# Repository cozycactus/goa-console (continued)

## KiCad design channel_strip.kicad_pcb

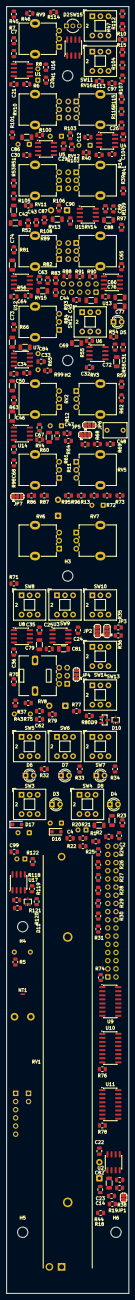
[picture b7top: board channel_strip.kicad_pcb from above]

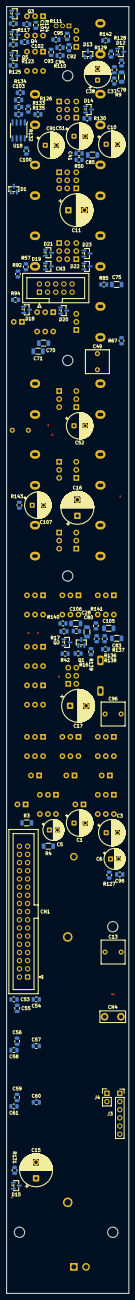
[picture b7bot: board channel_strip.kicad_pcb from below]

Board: 4 copper layers, 38.0 x 400.0 mm, 335 parts (105 on the bottom side), 195 nets, no tracks yet.

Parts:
C1, C3: 220u 25V; CP_Radial_D8.0mm_P3.50mm
C2, C4, C12, C20, C21, C22, C23, C24, C25, C26, C28, C29, C30, C31, C32, C33, C34, C35, C36, C53, C54, C55, C56, C57, C58, C59, C60, C61, C63, C64, C65, C66, C67, C68, C89, C90, C92, C93, C98, C100, C103, C104: 100n; C_0805_2012Metric
C5, C6: 47u 25V; CP_Radial_D6.3mm_P2.50mm
C7, C41: 33p C0G; C_0805_2012Metric
C10, C38, C51, C52, C91, C107: 33u NP 25V; CP_Radial_D8.0mm_P3.50mm
C11, C15, C16, C17: 100u NP 25V; CP_Radial_D10.0mm_P5.00mm
C13, C49, C96: 2.2u film; C_Rect_L7.2mm_W7.2mm_P5.00mm_FKS2_FKP2_MKS2_MKP2
C14, C94, C95: 100p C0G; C_0805_2012Metric
C37: 22p C0G; C_0805_2012Metric
C42, C43, C45: 4n7 C0G; C_1206_3216Metric
C44: 2n2 C0G; C_1206_3216Metric
C46: 10n C0G; C_1206_3216Metric
C47: 22n C0G; C_1206_3216Metric
C48: 150n film; C_Rect_L7.2mm_W4.5mm_P5.00mm_FKS2_FKP2_MKS2_MKP2
C50, C87, C88: 100n C0G; C_1206_3216Metric
C62: 1u; C_0805_2012Metric
C69, C70, C71, C72, C74, C76, C79, C80, C81, C82, C86: 10p C0G; C_1206_3216Metric
C73, C75, C77, C83, C85, C105, C106: 22p C0G; C_1206_3216Metric
C78: 33p C0G; C_1206_3216Metric
C84: 100p C0G; C_1206_3216Metric
C97, C99: 220n; C_0805_2012Metric
C101, C102: 10n; C_0805_2012Metric
CN1: Bus 2x17; IDC-Header_2x17_P2.54mm_Vertical
CN3: Jack board link 2x5; IDC-Header_2x05_P2.54mm_Vertical
CN4: Ground spade 6.3mm; Keystone_1287-ST_FastOn_Tab_6.35mm
D1, D12, D13, D14, D15: BAV99; SOT-23
D2: OL red / SIG green; LED_D3.0mm-3_P2.00mm
D3: PFL red; LED_D3.0mm
D4: ON green; LED_D3.0mm
D5: EQ green; LED_D3.0mm
D6: L-R yellow; LED_D3.0mm
D7: 1-2 yellow; LED_D3.0mm
D8: 3-4 yellow; LED_D3.0mm
D9: BZX84C5V1; SOT-23
D10, D11: BAT54W; SOT-323_SC-70
D16, D17: MBR140SFT1G; D_SOD-123F
D18, D19, D20, D21, D22, D23: BAV199; SOT-23
H1, H2, H3, H4, H5, H6: M3 standoff 11.5 mm; MountingHole_3.2mm_M3
J3: VCA module socket; PinSocket_1x06_P2.54mm_Vertical
J4: VCA control in; PinHeader_1x02_P2.54mm_Vertical
JP1: VCA bypass; SolderJumper-2_P1.3mm_Bridged_RoundedPad1.0x1.5mm
JP2: Aux1/2 pre source; SolderJumper-3_P1.3mm_Bridged12_RoundedPad1.0x1.5mm
JP3: Aux3/4 pre source; SolderJumper-3_P1.3mm_Bridged12_RoundedPad1.0x1.5mm
JP4: Aux5/6 pre source; SolderJumper-3_P1.3mm_Bridged12_RoundedPad1.0x1.5mm
JP5: Insert send source; SolderJumper-3_P1.3mm_Bridged12_RoundedPad1.0x1.5mm
JP6: EQ input; SolderJumper-3_P1.3mm_Bridged12_RoundedPad1.0x1.5mm
JP7: PRE source; SolderJumper-3_P1.3mm_Bridged12_RoundedPad1.0x1.5mm
NT1: AGND-LGND star; NetTie-2_SMD_Pad0.5mm
Q1, Q2: MMBFJ112; SOT-23
Q3, Q4, Q5: MMBT3906; SOT-23
R1, R2, R3, R4: 10R; R_1206_3216Metric
R5: 10R GND cancel; R_0805_2012Metric
R6, R7, R8, R9: 10K 0.1%; R_0805_2012Metric
R10, R112, R115, R121, R142: 1M; R_0805_2012Metric
R11, R71, R73: 75R; R_0805_2012Metric
R12, R13, R35, R36, R37, R47, R68, R72, R116, R117, R118, R122, R123, R125, R143: 47K; R_0805_2012Metric
R14, R134: 470K; R_0805_2012Metric
R15, R16, R17, R19, R34, R43, R69, R75, R77, R79, R80, R124: 4K7; R_0805_2012Metric
R18, R33, R44, R70, R74, R76, R78: 100K; R_0805_2012Metric
R20, R21, R22, R23, R24, R25, R32, R54, R55, R58, R59, R66, R67: 22K; R_0805_2012Metric
R26, R27, R28, R29, R30, R31: 4K7 1%; R_0805_2012Metric
R38, R137, R140: 2K2; R_0805_2012Metric
R39, R99, R126, R127, R128, R129, R130, R131, R135: 1K; R_0805_2012Metric
R40, R41, R120, R138, R141: 10K; R_0805_2012Metric
R42: 220K; R_0805_2012Metric
R45, R46, R84, R93: 2K2 1%; R_0805_2012Metric
R50, R51: 33K; R_0805_2012Metric
R52: 5K6; R_0805_2012Metric
R53: 6K8; R_0805_2012Metric
R56, R57, R100, R103: 4K99 1%; R_0805_2012Metric
R60, R61: 4K22 1%; R_0805_2012Metric
R62, R63, R136, R139: 3K3; R_0805_2012Metric
R64: 1K5; R_0805_2012Metric
R65: 5K1; R_0805_2012Metric
R81, R82, R83, R85, R90, R91, R92, R94: 10K 1%; R_0805_2012Metric
R86, R87: 392R 1%; R_0805_2012Metric
R88, R89, R97, R98, R105, R108: 13K 1%; R_0805_2012Metric
R95, R96: 430R 1%; R_0805_2012Metric
R101, R102: 2K49 1%; R_0805_2012Metric
R104, R107: 330R 1%; R_0805_2012Metric
R106, R109: 5K6 1%; R_0805_2012Metric
R110, R111: 220R; R_0805_2012Metric
R113, R114: 100R; R_0805_2012Metric
R119: 750K; R_0805_2012Metric
R132: 4M99 1%; R_0805_2012Metric
R133: 10M 1%; R_0805_2012Metric
RV1: Fader 10K log 100mm; Potentiometer_Bourns_PTB0143_Slide_100mm
RV2: Aux1 10K log; Potentiometer_Alpha_RD901F-40-00D_Single_Vertical
RV3: Aux2 10K log; Potentiometer_Alpha_RD901F-40-00D_Single_Vertical
RV4: Aux3 10K log; Potentiometer_Alpha_RD901F-40-00D_Single_Vertical
RV5: Aux4 10K log; Potentiometer_Alpha_RD901F-40-00D_Single_Vertical
RV6: Aux5 10K log; Potentiometer_Alpha_RD901F-40-00D_Single_Vertical
RV7: Aux6 10K log; Potentiometer_Alpha_RD901F-40-00D_Single_Vertical
RV8: Pan 10K lin dual CD; Potentiometer_Alps_RK09L_Double_Vertical
RV9: Gain 10K lin CD; Potentiometer_Alpha_RD901F-40-00D_Single_Vertical
RV10: HF 10K lin CD; Potentiometer_Alpha_RD901F-40-00D_Single_Vertical
RV11: HI-MID gain 10K lin CD; Potentiometer_Alpha_RD901F-40-00D_Single_Vertical
RV12: HI-MID freq 10K A dual; Potentiometer_Alpha_RD902F-40-00D_Dual_Vertical
RV13: LO-MID gain 10K lin CD; Potentiometer_Alpha_RD901F-40-00D_Single_Vertical
RV14: LO-MID freq 10K A dual; Potentiometer_Alpha_RD902F-40-00D_Dual_Vertical
RV15: LF 10K lin CD; Potentiometer_Alpha_RD901F-40-00D_Single_Vertical
RV16: HPF freq 10K A dual; Potentiometer_Alpha_RD902F-40-00D_Dual_Vertical
SW3: PFL; SW_Push_2P2T_Toggle_CK_PVA2xxH1xxxxxxV2
SW4: ON; SW_Push_2P2T_Toggle_CK_PVA2xxH1xxxxxxV2
SW5: Assign L-R; SW_Push_2P2T_Toggle_CK_PVA2xxH1xxxxxxV2
SW6: Assign 1-2; SW_Push_2P2T_Toggle_CK_PVA2xxH1xxxxxxV2
SW7: Assign 3-4; SW_Push_2P2T_Toggle_CK_PVA2xxH1xxxxxxV2
SW8: PRE 1-2; SW_Push_2P2T_Toggle_CK_PVA2xxH1xxxxxxV2
SW9: PRE 3-4; SW_Push_2P2T_Toggle_CK_PVA2xxH1xxxxxxV2
SW10: PRE 5-6; SW_Push_2P2T_Toggle_CK_PVA2xxH1xxxxxxV2
SW11: HPF; SW_Push_2P2T_Toggle_CK_PVA2xxH1xxxxxxV2
SW12: EQ; SW_Push_2P2T_Toggle_CK_PVA2xxH1xxxxxxV2
SW13: DIR; SW_Push_2P2T_Toggle_CK_PVA2xxH1xxxxxxV2
SW14: PAN; SW_Push_2P2T_Toggle_CK_PVA2xxH1xxxxxxV2
SW15: Phase; SW_Push_2P2T_Toggle_CK_PVA2xxH1xxxxxxV2
U1, U2, U3, U5, U6, U7, U8, U12, U13, U14, U15: OPA1612; SOIC-8_3.9x4.9mm_P1.27mm
U4, U17, U18: LM393; SOIC-8_3.9x4.9mm_P1.27mm
U9, U10, U11: DG413; SOIC-16_3.9x9.9mm_P1.27mm
U16: OPA1656; SOIC-8_3.9x4.9mm_P1.27mm

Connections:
+5VL: C55.1, C58.1, C61.1, C62.1, D9.3, D10.1, R80.2, SW5.1, SW6.1, SW7.1, U9.12, U10.12, U11.12
+VA: C1.1, C2.1, C20.1, C22.1, C24.1, C29.1, C31.1, C33.1, C35.1, C53.1, C56.1, C59.1, C63.1, C65.1, C67.1, C89.1, C92.1, D10.3, D16.1, D18.2, D19.2, D20.2, D21.2, D22.2, D23.2, J3.4, R1.2, R80.1, U1.8, U2.8, U3.8, U5.8, U6.8, U7.8, U8.8, U9.13, U10.13, U11.13, U12.8, U13.8, U14.8, U15.8, U16.8
+VBUS: CN1.32, CN1.33, CN1.34, R1.1, R3.1
+VL: C5.1, C26.1, C98.1, C101.2, C102.2, C104.1, Q3.2, Q4.2, Q5.2, R3.2, R40.1, R115.1, R117.1, R121.1, R123.1, R132.1, SW3.5, SW4.5, SW5.5, SW6.5, SW7.5, SW12.5, U4.8, U17.8, U18.8
-VA: C3.2, C4.2, C21.2, C23.2, C25.2, C30.2, C32.2, C34.2, C36.2, C54.2, C57.2, C60.2, C64.2, C66.2, C68.2, C90.2, C93.2, D17.2, D18.1, D19.1, D20.1, D21.1, D22.1, D23.1, J3.6, R2.2, U1.4, U2.4, U3.4, U5.4, U6.4, U7.4, U8.4, U9.4, U10.4, U11.4, U12.4, U13.4, U14.4, U15.4, U16.4
-VBUS: CN1.30, CN1.31, R2.1, R4.1
-VL: C6.2, R4.2, SW4.1
A6R: R25.1, SW13.3, SW13.5
AUX1: CN1.24, R20.2
AUX2: CN1.25, R21.2
AUX3: CN1.23, R22.2
AUX4: CN1.22, R23.2
AUX5: CN1.21, R24.2
AUX6: CN1.20, R25.2
BUF1: JP6.3, JP7.1, U7.6, U7.7
DIRSRC: C83.1, R70.1, SW13.1, U8.3
DO_R: CN3.9, D23.3, R73.1, R143.1
DO_T: C52.2, CN3.8, D22.3, R72.1
EQIN: JP6.2, R50.1, RV10.3, SW12.3
EQOUT: C51.2, JP5.1, JP7.3, R68.1, R130.1
EQ_FP: C49.2, C50.1, R65.1, U7.3
EQ_LP: C46.1, R93.1, R98.1, RV14.6, U6.5, U14.1
EQ_MP: C44.1, R84.1, R89.1, RV12.6, U6.3, U12.7
EQ_O6: C73.1, R63.2, R67.1, SW12.1, U7.1
EQ_WHM: R81.1, RV11.2
EQ_WLM: R90.1, RV13.2
FPIN: C82.1, J3.2, JP1.2, R18.1, U2.3
FPOST: C14.1, C15.1, R19.1, R131.1, U2.1
GCANCEL: CN1.26, R5.2
GNDA: C1.2, C2.2, C3.1, C4.1, C12.2, C20.2, C21.1, C22.2, C23.1, C24.2, C25.1, C28.2, C29.2, C30.1, C31.2, C32.1, C33.2, C34.1, C35.2, C36.1, C50.2, C53.2, C54.1, C56.2, C57.1, C59.2, C60.1, C63.2, C64.1, C65.2, C66.1, C67.2, C68.1, C75.2, C77.2, C78.2, C79.2, C80.2, C81.2, C82.2, C83.2, C84.2, C85.2, C89.2, C90.1, C92.2, C93.1, C94.2, C95.2, C100.2, C103.2, C107.2, CN1.2, CN1.4, CN1.6, CN1.8, CN1.10, CN1.12, CN1.14, CN1.16, CN3.3, CN3.5, CN3.7, CN3.10, CN4.1, D16.2, D17.1, J3.5, J4.2, NT1.1, Q1.2, Q2.2, R5.1, R9.2, R10.2, R12.2, R13.2, R14.2, R18.2, R35.2, R36.2, R37.2, R38.2, R41.2, R44.2, R47.2, R52.2, R65.2, R68.2, R70.2, R72.2, R85.2, R86.2, R87.2, R94.2, R95.2, R96.2, R104.2, R107.2, R112.2, R120.2, R134.2, R138.1, R141.1, R143.2, RV1.1, RV2.1, RV3.1, RV4.1, RV5.1, RV6.1, RV7.1, RV8.3, RV8.4, SW3.3, SW13.4, U1.5, U2.5, U5.5, U9.10, U9.15, U10.10, U10.15, U11.10, U11.15, U12.5, U13.3, U14.3, U14.5, U15.3, U15.5
GNDD: C5.2, C6.1, C26.2, C55.2, C58.2, C61.2, C62.2, C97.2, C98.2, C99.2, C104.2, D2.2, D3.1, D4.1, D5.1, D6.1, D7.1, D8.1, D9.1, D11.1, NT1.2, R74.2, R76.2, R78.2, SW4.3, SW5.3, SW6.3, SW7.3, U4.4, U9.5, U10.5, U11.5, U17.4, U18.4, U18.6
GOUT: C37.1, C38.1, C91.1, R46.2, R129.1, R142.2, U1.7
HIN: C38.2, C91.2, R47.1, R100.1, SW11.3
HOUT: JP2.3, JP3.3, JP4.3, JP5.3, JP6.1, SW11.2
INS_SRC: JP5.2, R11.1
IN_R: CN3.2, D19.3, R111.1, R112.1
IN_T: CN3.1, D18.3, R10.1, R110.1
MIXL: CN1.18, U9.2
MIXR: CN1.17, U9.7
MUTEOUT: JP2.1, JP3.1, JP4.1, RV1.3, U3.6, U3.7
unnamed: C10.2, R12.1, R99.1
unnamed: C13.1, RV1.2
unnamed: C41.1, C69.1, R51.1, R54.1, RV10.1, RV11.1, U5.7
unnamed: C42.1, RV10.2
unnamed: C42.2, C43.1, R52.1
unnamed: C43.2, R53.1
unnamed: C45.1, R82.1, U13.1
unnamed: C47.1, R91.1, U14.7
unnamed: C48.1, R62.2, RV15.1
unnamed: C48.2, R63.1, RV15.3
unnamed: C49.1, R64.2
unnamed: C52.1, R71.2
unnamed: C70.1, C71.1, R55.1, R58.1, RV11.3, RV13.1, U6.1
unnamed: C72.1, R59.1, R62.1, R66.1, RV13.3, U6.7
unnamed: C74.1, R83.1, R88.1, RV12.3, U12.1
unnamed: C76.1, R92.1, R97.1, RV14.3, U13.7
unnamed: C87.1, R101.1, R108.1, RV16.6, U15.1
unnamed: C88.1, R102.1, U15.7
unnamed: C96.2, R32.1
unnamed: C16.1, C105.2, R136.1, R137.2, U8.7
unnamed: C17.1, C106.2, R139.1, R140.2, U3.1
unnamed: C107.1, R73.2
unnamed: D1.3, R39.2
unnamed: D3.2, R34.2
unnamed: D4.2, R43.2
unnamed: D5.2, R69.2
unnamed: D6.2, R75.2
unnamed: D7.2, R77.2
unnamed: D8.2, R79.2
unnamed: D12.3, R128.2
unnamed: D13.3, R129.2
unnamed: D14.3, R130.2
unnamed: D15.3, R131.2
unnamed: JP2.2, SW8.1
unnamed: JP3.2, SW9.1
unnamed: JP4.2, SW10.1
unnamed: Q1.1, R16.2, R17.1
unnamed: C28.1, Q1.3, Q2.3, R42.2
unnamed: C81.1, Q2.1, R17.2, U3.5
unnamed: C101.1, Q3.1, R116.2, R117.2
unnamed: Q3.3, R15.1
unnamed: Q4.3, R124.1
unnamed: Q5.1, R125.2
unnamed: R20.1, RV2.2
unnamed: R21.1, RV3.2
unnamed: R22.1, RV4.2
unnamed: R23.1, RV5.2
unnamed: R24.1, RV6.2
unnamed: R26.2, U9.3, U9.14
unnamed: R27.2, U9.6, U9.11
unnamed: R28.2, U10.3, U10.14
unnamed: R29.2, U10.6, U10.11
unnamed: R30.2, U11.3, U11.14
unnamed: R31.2, U11.6, U11.11
unnamed: R45.2, RV9.3
unnamed: R46.1, RV9.1
unnamed: R56.1, R88.2, RV12.2
unnamed: R57.1, R89.2, RV12.5
unnamed: R60.1, R97.2, RV14.2
unnamed: R61.1, R98.2, RV14.5
unnamed: R64.1, RV15.2
unnamed: R86.1, RV12.1
unnamed: R87.1, RV12.4
unnamed: R95.1, RV14.1
unnamed: R96.1, RV14.4
unnamed: R104.1, RV16.1
unnamed: R105.2, R106.1, RV16.2
unnamed: R107.1, RV16.4
unnamed: R108.2, R109.1, RV16.5
unnamed: R122.1, U17.7
unnamed: R126.1, U4.1
unnamed: R127.1, U17.1
unnamed: R135.1, U18.1
unnamed: R32.2, SW3.2
unnamed: R33.1, R34.1, SW3.4
unnamed: R42.1, SW4.2
unnamed: R43.1, SW4.4
unnamed: R75.1, SW5.4
unnamed: R77.1, SW6.4
unnamed: R79.1, SW7.4
unnamed: RV2.3, RV3.3, SW8.2
unnamed: RV4.3, RV5.3, SW9.2
unnamed: RV6.3, RV7.3, SW10.2
unnamed: C86.1, R103.1, R105.1, RV16.3, SW11.1, U5.1
unnamed: C51.1, SW12.2
unnamed: R69.1, SW12.4
unnamed: RV7.2, SW13.2
unnamed: R114.2, SW15.1, SW15.6
unnamed: R6.1, SW15.2
unnamed: R113.2, SW15.3, SW15.4
unnamed: R8.1, SW15.5
unnamed: C78.1, R8.2, R9.1, U1.3
unnamed: C7.1, R6.2, R7.1, U1.2
unnamed: C37.2, R142.1, RV9.2, U1.6
unnamed: C14.2, R19.2, R38.1, U2.2
unnamed: U2.6, U2.7
unnamed: C80.1, R139.2, RV8.5, U3.3
unnamed: C106.1, R140.1, R141.2, U3.2
unnamed: C85.1, R100.2, R101.2, U5.3
unnamed: C86.2, R102.2, R103.2, U5.2
unnamed: C41.2, R50.2, R51.2, R53.2, U5.6
unnamed: C69.2, C70.2, R54.2, R55.2, U6.2
unnamed: C71.2, C72.2, R58.2, R59.2, U6.6
unnamed: C73.2, R66.2, R67.2, U7.2
unnamed: C84.1, R99.2, U7.5
unnamed: R71.1, U8.1, U8.2
unnamed: C79.1, R136.2, RV8.2, U8.5
unnamed: C105.1, R137.1, R138.2, U8.6
unnamed: C75.1, R84.2, R85.1, U12.3
unnamed: C74.2, R81.2, R82.2, R83.2, U12.2
unnamed: C44.2, R56.2, U12.6
unnamed: C45.2, R57.2, U13.2
unnamed: C77.1, R93.2, R94.1, U13.5
unnamed: C76.2, R90.2, R91.2, R92.2, U13.6
unnamed: C46.2, R60.2, U14.2
unnamed: C47.2, R61.2, U14.6
unnamed: C87.2, R106.2, U15.2
unnamed: C88.2, R109.2, U15.6
unnamed: C94.1, R110.2, U16.3
unnamed: R113.1, U16.1, U16.2
unnamed: C95.1, R111.2, U16.5
unnamed: R114.1, U16.6, U16.7
unnamed: R119.2, R120.1, U17.3
unnamed: C99.1, R121.2, R127.2, U17.5
unnamed: R132.2, R133.1, U18.3
OL_A: D2.1, R15.2
OL_HOLD: C97.1, R115.2, R126.2, R135.2, U4.5
OL_K: R116.1, R125.1, U4.7
OL_NN: C103.1, D1.1, D12.1, D13.1, D14.1, D15.1, R133.2, R134.1
PANL: C16.2, R26.1, R36.1, SW14.1
PANR: C17.2, R27.1, R37.1, SW14.4
PFL: CN1.27, SW3.1
PFLDET: CN1.29, R33.2
PK: C12.1, D1.2, D12.2, D13.2, D14.2, D15.2, R14.1, U4.2
POST: C15.2, R35.1, RV8.1, RV8.6, SW8.3, SW9.3, SW10.3, SW14.3, SW14.6
PRE: C11.2, C96.1, R13.1, R16.1
PRESRC: C11.1, JP7.2, R39.1, R118.1
RECV: C7.2, R7.2, R45.1, R128.1, U1.1
RET_RAW: C10.1, CN3.6, D20.3
RTE_12: R76.1, SW6.2, U10.1, U10.8, U10.9, U10.16
RTE_34: R78.1, SW7.2, U11.1, U11.8, U11.9, U11.16
RTE_LR: R74.1, SW5.2, U9.1, U9.8, U9.9, U9.16
SEND: CN3.4, D21.3, R11.2
SIG_A: D2.3, R124.2
SIG_B: C102.1, Q4.1, Q5.3, R122.2, R123.2
SIG_IN: D11.3, R118.2, U17.2
SUB1: CN1.15, U10.2
SUB2: CN1.13, U10.7
SUB3: CN1.11, U11.2
SUB4: CN1.9, U11.7
SUBSRC_L: R28.1, R30.1, SW14.2
SUBSRC_R: R29.1, R31.1, SW14.5
VCAIN: C13.2, J3.1, JP1.1
VCA_CTRL: J3.3, J4.1, R44.1
VREF: C100.1, R40.2, R41.1, R119.1, U4.3, U4.6, U17.6, U18.2, U18.5

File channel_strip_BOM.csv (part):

"Qty","Value","Footprint","MPN","DNP","References"
"2","220u 25V","Capacitor_THT:CP_Radial_D8.0mm_P3.50mm","Rubycon 35ZLH220MEFC8X11.5 (35V)","","C1 C3"
"42","100n","Capacitor_SMD:C_0805_2012Metric","Samsung CL21B104KBCNNNC (X7R 50V)","","C2 C4 C12 C20 C21 C22 C23 C24 C25 C26 C28 C29 C30 C31 C32 C33 C34 C35 C36 C53 C54 C55 C56 C57 C58 C59 C60 C61 C63 C64 C65 C66 C67 C68 C89 C90 C92 C93 C98 C100 C103 C104"
"2","47u 25V","Capacitor_THT:CP_Radial_D6.3mm_P2.50mm","Panasonic EEU-FR1H470 (50V)","","C5 C6"
"2","33p C0G","Capacitor_SMD:C_0805_2012Metric","KEMET C0805C330J5GACTU","","C7 C41"
"6","33u NP 25V","Capacitor_THT:CP_Radial_D8.0mm_P3.50mm","Nichicon UES1E330MPM (MUSE ES)","","C10 C38 C51 C52 C91 C107"
"4","100u NP 25V","Capacitor_THT:CP_Radial_D10.0mm_P5.00mm","Nichicon UES1E101MPM (MUSE ES)","","C11 C15 C16 C17"
"3","2.2u film","Capacitor_THT:C_Rect_L7.2mm_W7.2mm_P5.00mm_FKS2_FKP2_MKS2_MKP2","KEMET MMK5225K63J06L4BULK (PET 63V; replaces the obsolete WIMA MKS2C042201K00KSSD)","","C13 C49 C96"
"3","100p C0G","Capacitor_SMD:C_0805_2012Metric","KEMET C0805C101J5GACTU","","C14 C94 C95"
"1","22p C0G","Capacitor_SMD:C_0805_2012Metric","KEMET C0805C220J5GACTU","","C37"
"3","4n7 C0G","Capacitor_SMD:C_1206_3216Metric","KEMET C1206C472J5GACTU","","C42 C43 C45"
"1","2n2 C0G","Capacitor_SMD:C_1206_3216Metric","KEMET C1206C222J5GACTU","","C44"
"1","10n C0G","Capacitor_SMD:C_1206_3216Metric","KEMET C1206C103J5GACTU","","C46"
"1","22n C0G","Capacitor_SMD:C_1206_3216Metric","KEMET C1206C223J5GACTU","","C47"
"1","150n film","Capacitor_THT:C_Rect_L7.2mm_W4.5mm_P5.00mm_FKS2_FKP2_MKS2_MKP2","WIMA MKS2D031501C00KSSD (PET 100V; 3.5 x 8.5 x 7.2, the 63 V KSSD code has no stock)","","C48"
"3","100n C0G","Capacitor_SMD:C_1206_3216Metric","Murata GRM31C5C1H104JA01L","","C50 C87 C88"
"1","1u","Capacitor_SMD:C_0805_2012Metric","Murata GRM21BR71H105KA12L (X7R 50V)","","C62"
"11","10p C0G","Capacitor_SMD:C_1206_3216Metric","KEMET C1206C100J5GACTU","","C69 C70 C71 C72 C74 C76 C79 C80 C81 C82 C86"
"7","22p C0G","Capacitor_SMD:C_1206_3216Metric","KEMET C1206C220J5GACTU","","C73 C75 C77 C83 C85 C105 C106"
"1","33p C0G","Capacitor_SMD:C_1206_3216Metric","KEMET C1206C330J5GACTU","","C78"
"1","100p C0G","Capacitor_SMD:C_1206_3216Metric","KEMET C1206C101J5GACTU","","C84"
"2","220n","Capacitor_SMD:C_0805_2012Metric","Samsung CL21B224KBFNNNE (X7R 50V)","","C97 C99"
"2","10n","Capacitor_SMD:C_0805_2012Metric","Samsung CL21B103KBANNNC (X7R 50V)","","C101 C102"
"1","Bus 2x17","Connector_IDC:IDC-Header_2x17_P2.54mm_Vertical","Wurth 61203421621 (2x17 box header)","","CN1"
"1","Jack board link 2x5","Connector_IDC:IDC-Header_2x05_P2.54mm_Vertical","Wurth 61201021621 (2x5 box header)","","CN3"
"1","Ground spade 6.3mm","goa-console:Keystone_1287-ST_FastOn_Tab_6.35mm","Keystone 1287-ST","","CN4"
"5","BAV99","Package_TO_SOT_SMD:SOT-23","Nexperia BAV99,215","","D1 D12 D13 D14 D15"
"1","OL red / SIG green","goa-console:LED_D3.0mm-3_P2.00mm","Kingbright WP3VEGW","","D2"
"1","PFL red","LED_THT:LED_D3.0mm","Kingbright WP710A10ID","","D3"
"1","ON green","LED_THT:LED_D3.0mm","Kingbright WP710A10GD","","D4"
"1","EQ green","LED_THT:LED_D3.0mm","Kingbright WP710A10GD","","D5"
"1","L-R yellow","LED_THT:LED_D3.0mm","Kingbright WP710A10YD","","D6"
"1","1-2 yellow","LED_THT:LED_D3.0mm","Kingbright WP710A10YD","","D7"
"1","3-4 yellow","LED_THT:LED_D3.0mm","Kingbright WP710A10YD","","D8"
"1","BZX84C5V1","Package_TO_SOT_SMD:SOT-23","Nexperia BZX84-C5V1,215","","D9"
"2","BAT54W","Package_TO_SOT_SMD:SOT-323_SC-70","Nexperia BAT54W,115","","D10 D11"
"2","PMEG4010CEH","Diode_SMD:D_SOD-123F","Nexperia PMEG4010CEH,115","","D16 D17"
"6","BAV199","Package_TO_SOT_SMD:SOT-23","Nexperia BAV199,215","","D18 D19 D20 D21 D22 D23"
"1","VCA module socket","Connector_PinSocket_2.54mm:PinSocket_1x06_P2.54mm_Vertical","","DNP","J3"
"1","VCA control in","Connector_PinHeader_2.54mm:PinHeader_1x02_P2.54mm_Vertical","","DNP","J4"
"2","MMBFJ112","Package_TO_SOT_SMD:SOT-23","onsemi MMBFJ112","","Q1 Q2"
"3","MMBT3906","Package_TO_SOT_SMD:SOT-23","onsemi MMBT3906LT1G","","Q3 Q4 Q5"
"4","10R","Resistor_SMD:R_1206_3216Metric","Vishay M251206BB1009JP500","","R1 R2 R3 R4"
"1","10R GND cancel","Resistor_SMD:R_0805_2012Metric","","","R5"
"4","10K 0.1%","Resistor_SMD:R_0805_2012Metric","Panasonic ERA-6AEB103V","","R6 R7 R8 R9"
"5","1M","Resistor_SMD:R_0805_2012Metric","","","R10 R112 R115 R121 R142"
"3","75R","Resistor_SMD:R_0805_2012Metric","Panasonic ERJ-P06J750V","","R11 R71 R73"
"15","47K","Resistor_SMD:R_0805_2012Metric","","","R12 R13 R35 R36 R37 R47 R68 R72 R116 R117 R118 R122 R123 R125 R143"
"2","470K","Resistor_SMD:R_0805_2012Metric","","","R14 R134"
"12","4K7","Resistor_SMD:R_0805_2012Metric","","","R15 R16 R17 R19 R34 R43 R69 R75 R77 R79 R80 R124"
"6","100K","Resistor_SMD:R_0805_2012Metric","","","R18 R33 R70 R74 R76 R78"
"13","22K","Resistor_SMD:R_0805_2012Metric","","","R20 R21 R22 R23 R24 R25 R32 R54 R55 R58 R59 R66 R67"
"6","4K7 1%","Resistor_SMD:R_0805_2012Metric","","","R26 R27 R28 R29 R30 R31"
"3","2K2","Resistor_SMD:R_0805_2012Metric","","","R38 R137 R140"
"9","1K","Resistor_SMD:R_0805_2012Metric","","","R39 R99 R126 R127 R128 R129 R130 R131 R135"
"5","10K","Resistor_SMD:R_0805_2012Metric","","","R40 R41 R120 R138 R141"
"1","220K","Resistor_SMD:R_0805_2012Metric","","","R42"
"1","100K","Resistor_SMD:R_0805_2012Metric","","DNP","R44"
"4","2K2 1%","Resistor_SMD:R_0805_2012Metric","","","R45 R46 R84 R93"
"2","33K","Resistor_SMD:R_0805_2012Metric","","","R50 R51"
"1","5K6","Resistor_SMD:R_0805_2012Metric","","","R52"
"1","6K8","Resistor_SMD:R_0805_2012Metric","","","R53"
"4","4K99 1%","Resistor_SMD:R_0805_2012Metric","","","R56 R57 R100 R103"
"2","4K22 1%","Resistor_SMD:R_0805_2012Metric","","","R60 R61"
"4","3K3","Resistor_SMD:R_0805_2012Metric","","","R62 R63 R136 R139"
"1","1K5","Resistor_SMD:R_0805_2012Metric","","","R64"
"1","5K1","Resistor_SMD:R_0805_2012Metric","","","R65"
"8","10K 1%","Resistor_SMD:R_0805_2012Metric","","","R81 R82 R83 R85 R90 R91 R92 R94"
"2","392R 1%","Resistor_SMD:R_0805_2012Metric","","","R86 R87"
"6","13K 1%","Resistor_SMD:R_0805_2012Metric","","","R88 R89 R97 R98 R105 R108"
"2","430R 1%","Resistor_SMD:R_0805_2012Metric","","","R95 R96"
"2","2K49 1%","Resistor_SMD:R_0805_2012Metric","","","R101 R102"
"2","330R 1%","Resistor_SMD:R_0805_2012Metric","","","R104 R107"
"2","5K6 1%","Resistor_SMD:R_0805_2012Metric","","","R106 R109"
"2","220R","Resistor_SMD:R_0805_2012Metric","","","R110 R111"
"2","100R","Resistor_SMD:R_0805_2012Metric","","","R113 R114"
"1","750K","Resistor_SMD:R_0805_2012Metric","","","R119"
"1","4M99 1%","Resistor_SMD:R_0805_2012Metric","","","R132"
"1","10M 1%","Resistor_SMD:R_0805_2012Metric","","","R133"
"1","Fader 10K log 100mm","goa-console:Potentiometer_Bourns_PTB0143_Slide_100mm","Bourns PTB0143-2010BPA103","","RV1"
"1","Aux1 10K log","Potentiometer_THT:Potentiometer_Alpha_RD901F-40-00D_Single_Vertical","Alpha RD901F-40-15R1-A10K","","RV2"
"1","Aux2 10K log","Potentiometer_THT:Potentiometer_Alpha_RD901F-40-00D_Single_Vertical","Alpha RD901F-40-15R1-A10K","","RV3"
"1","Aux3 10K log","Potentiometer_THT:Potentiometer_Alpha_RD901F-40-00D_Single_Vertical","Alpha RD901F-40-15R1-A10K","","RV4"
"1","Aux4 10K log","Potentiometer_THT:Potentiometer_Alpha_RD901F-40-00D_Single_Vertical","Alpha RD901F-40-15R1-A10K","","RV5"
"1","Aux5 10K log","Potentiometer_THT:Potentiometer_Alpha_RD901F-40-00D_Single_Vertical","Alpha RD901F-40-15R1-A10K","","RV6"
"1","Aux6 10K log","Potentiometer_THT:Potentiometer_Alpha_RD901F-40-00D_Single_Vertical","Alpha RD901F-40-15R1-A10K","","RV7"
"1","Pan 10K lin dual CD","Potentiometer_THT:Potentiometer_Alps_RK09L_Double_Vertical","ALPS RK09L1240015","","RV8"
"1","Gain 10K lin CD","Potentiometer_THT:Potentiometer_Alpha_RD901F-40-00D_Single_Vertical","Alpha RD901F-40-15R1-B10K-0CD (centre detent)","","RV9"
"1","HF 10K lin CD","Potentiometer_THT:Potentiometer_Alpha_RD901F-40-00D_Single_Vertical","Alpha RD901F-40-15R1-B10K-0CD (centre detent)","","RV10"
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
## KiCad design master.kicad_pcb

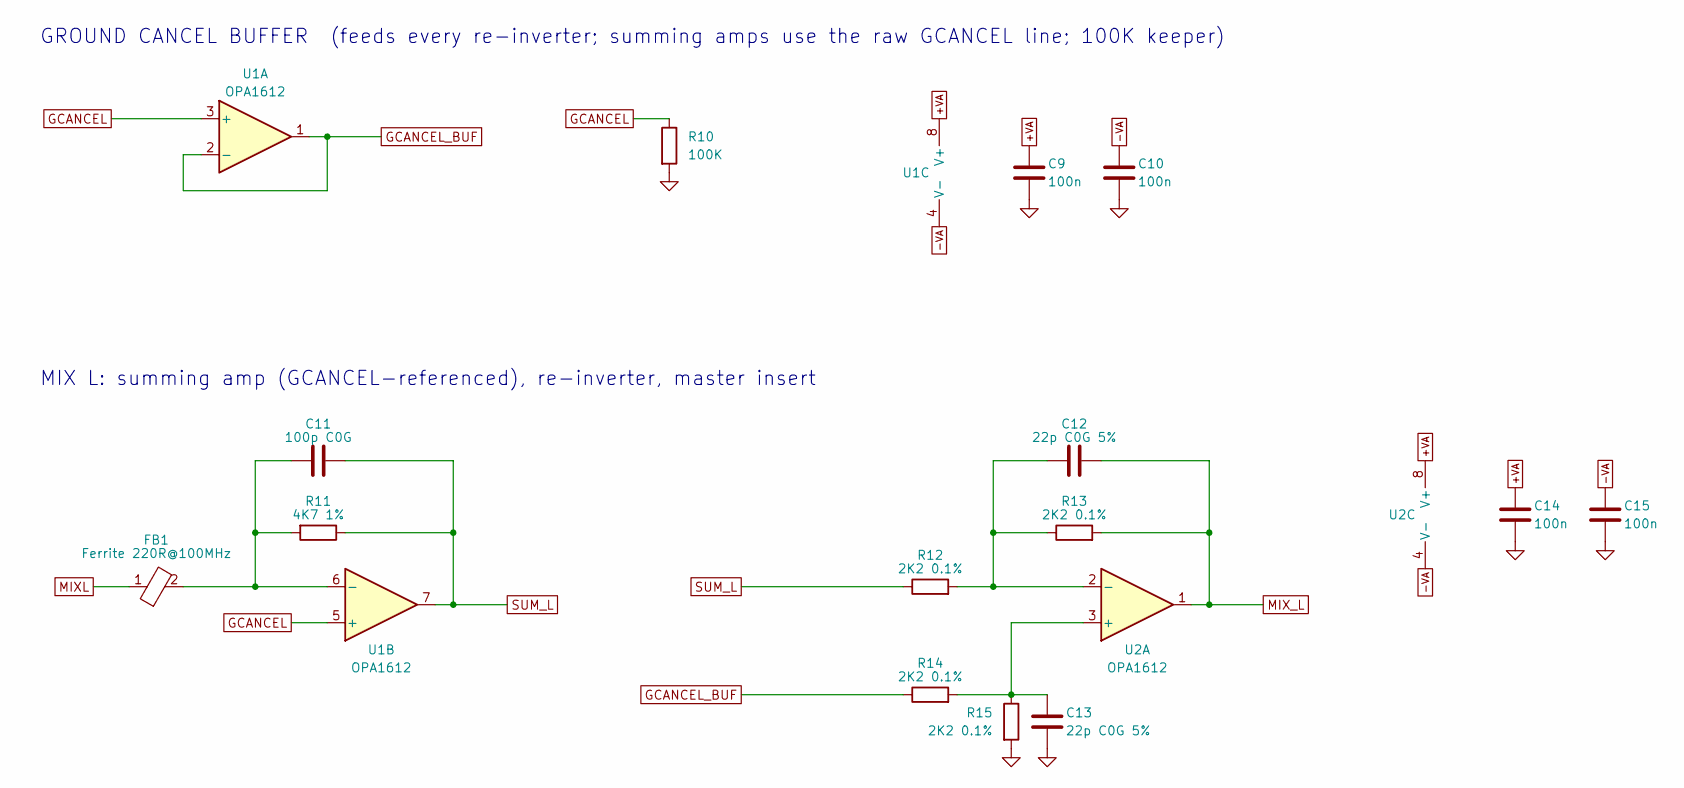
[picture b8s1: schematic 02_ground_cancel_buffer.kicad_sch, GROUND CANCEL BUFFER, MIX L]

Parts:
C9, C10, C14, C15: 100n; C_0805_2012Metric; MPN Samsung CL21B104KBCNNNC (X7R 50V)
C11: 100p C0G; C_0805_2012Metric; MPN KEMET C0805C101J5GACTU
C12, C13: 22p C0G 5%; C_0805_2012Metric; MPN KEMET C0805C220J5GACTU
FB1: Ferrite 220R@100MHz; L_0805_2012Metric; MPN Murata BLM21PG221SN1D
R10: 100K; R_0805_2012Metric
R11: 4K7 1%; R_0805_2012Metric
R12, R13, R14, R15: 2K2 0.1%; R_0805_2012Metric; MPN Panasonic ERA-6AEB222V
U1, U2: OPA1612; SOIC-8_3.9x4.9mm_P1.27mm; MPN TI OPA1612AIDR

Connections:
+VA: C9.1, C14.1, U1.8 (V+), U2.8 (V+); also elsewhere on the board
-VA: C10.2, C15.2, U1.4 (V-), U2.4 (V-); also elsewhere on the board
GCANCEL: R10.1, U1.3 (+), U1.5 (+); also elsewhere on the board
GCANCEL_BUF: R14.1, U1.1, U1.2 (-); also elsewhere on the board
MIXL: FB1.1; also elsewhere on the board
MIX_L: C12.1, R13.2, U2.1; also elsewhere on the board
unnamed: C11.2, FB1.2, R11.2, U1.6 (-)
unnamed: C13.1, R14.2, R15.1, U2.3 (+)
unnamed: C12.2, R12.2, R13.1, U2.2 (-)
SUM_L: C11.1, R11.1, R12.1, U1.7

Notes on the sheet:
GROUND CANCEL BUFFER (feeds every re-inverter; summing amps use the raw GCANCEL line; 100K keeper)
MIX L: summing amp (GCANCEL-referenced), re-inverter, master insert

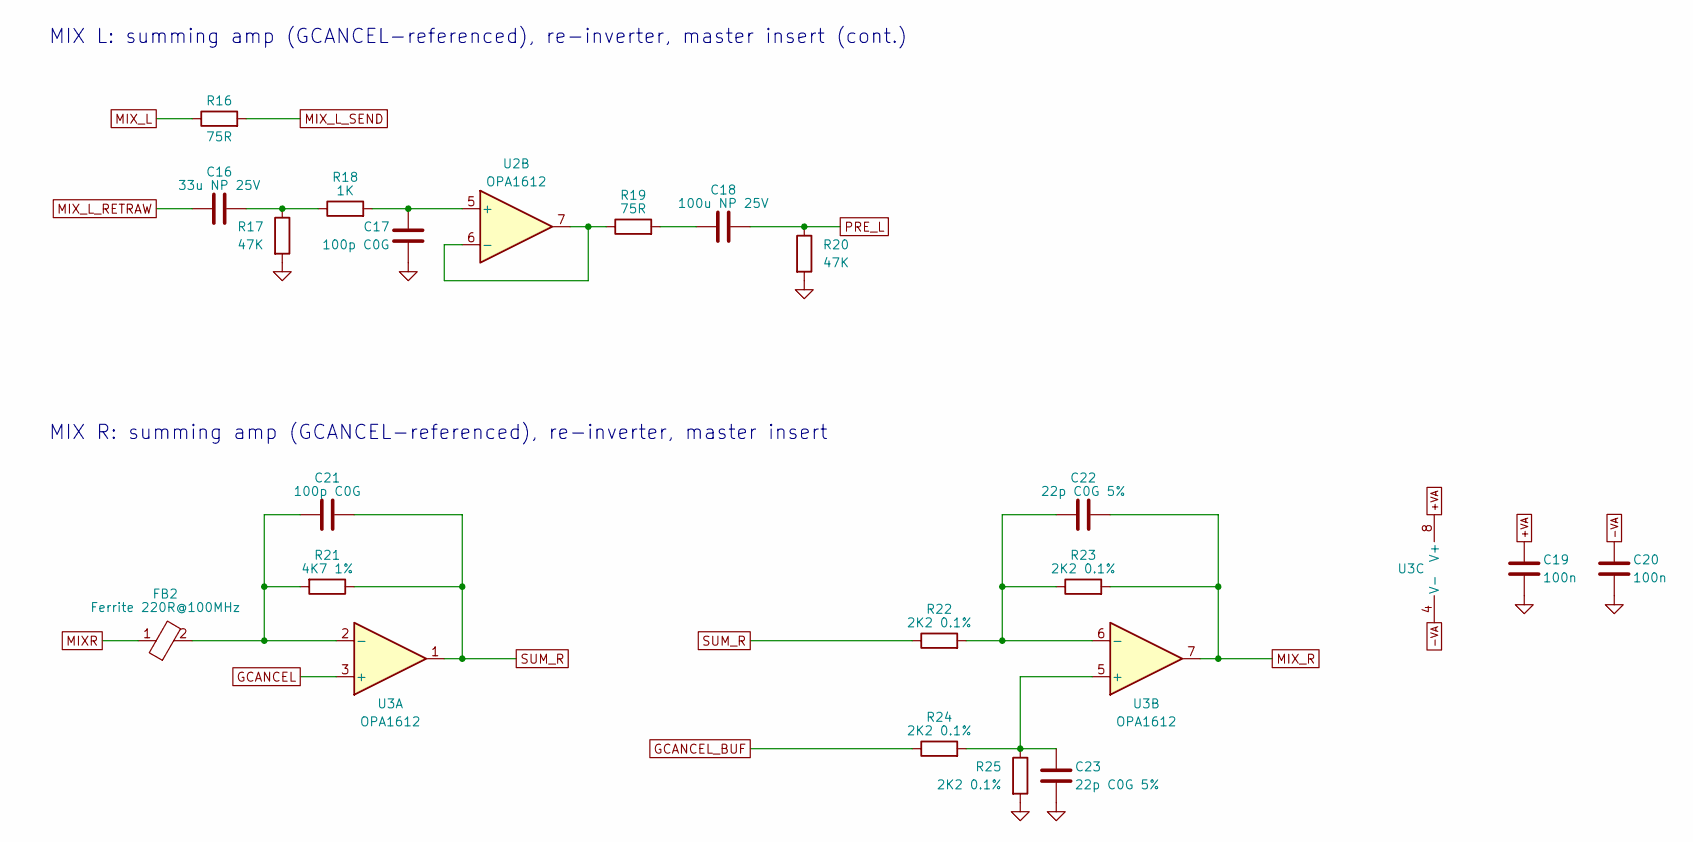
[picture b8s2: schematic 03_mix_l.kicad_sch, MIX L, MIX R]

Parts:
C16: 33u NP 25V; CP_Radial_D8.0mm_P3.50mm; MPN Nichicon UES1E330MPM (MUSE ES)
C17, C21: 100p C0G; C_0805_2012Metric; MPN KEMET C0805C101J5GACTU
C18: 100u NP 25V; CP_Radial_D10.0mm_P5.00mm; MPN Nichicon UES1E101MPM (MUSE ES)
C19, C20: 100n; C_0805_2012Metric; MPN Samsung CL21B104KBCNNNC (X7R 50V)
C22, C23: 22p C0G 5%; C_0805_2012Metric; MPN KEMET C0805C220J5GACTU
FB2: Ferrite 220R@100MHz; L_0805_2012Metric; MPN Murata BLM21PG221SN1D
R16: 75R; R_0805_2012Metric; MPN Panasonic ERJ-P06J750V
R17, R20: 47K; R_0805_2012Metric
R18: 1K; R_0805_2012Metric
R19: 75R; R_0805_2012Metric
R21: 4K7 1%; R_0805_2012Metric
R22, R23, R24, R25: 2K2 0.1%; R_0805_2012Metric; MPN Panasonic ERA-6AEB222V
U2, U3: OPA1612; SOIC-8_3.9x4.9mm_P1.27mm; MPN TI OPA1612AIDR

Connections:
+VA: C19.1, U3.8 (V+); also elsewhere on the board
-VA: C20.2, U3.4 (V-); also elsewhere on the board
GCANCEL: U3.3 (+); also elsewhere on the board
GCANCEL_BUF: R24.1; also elsewhere on the board
MIXR: FB2.1; also elsewhere on the board
MIX_L: R16.1; also elsewhere on the board
MIX_L_RETRAW: C16.1; also elsewhere on the board
MIX_L_SEND: R16.2; also elsewhere on the board
MIX_R: C22.1, R23.2, U3.7; also elsewhere on the board
unnamed: C16.2, R17.1, R18.1
unnamed: C18.1, R19.2
unnamed: C17.1, R18.2, U2.5 (+)
unnamed: R19.1, U2.6 (-), U2.7
unnamed: C21.2, FB2.2, R21.2, U3.2 (-)
unnamed: C23.1, R24.2, R25.1, U3.5 (+)
unnamed: C22.2, R22.2, R23.1, U3.6 (-)
PRE_L: C18.2, R20.1; also elsewhere on the board
SUM_R: C21.1, R21.1, R22.1, U3.1

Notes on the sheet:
MIX L: summing amp (GCANCEL-referenced), re-inverter, master insert (cont.)
MIX R: summing amp (GCANCEL-referenced), re-inverter, master insert

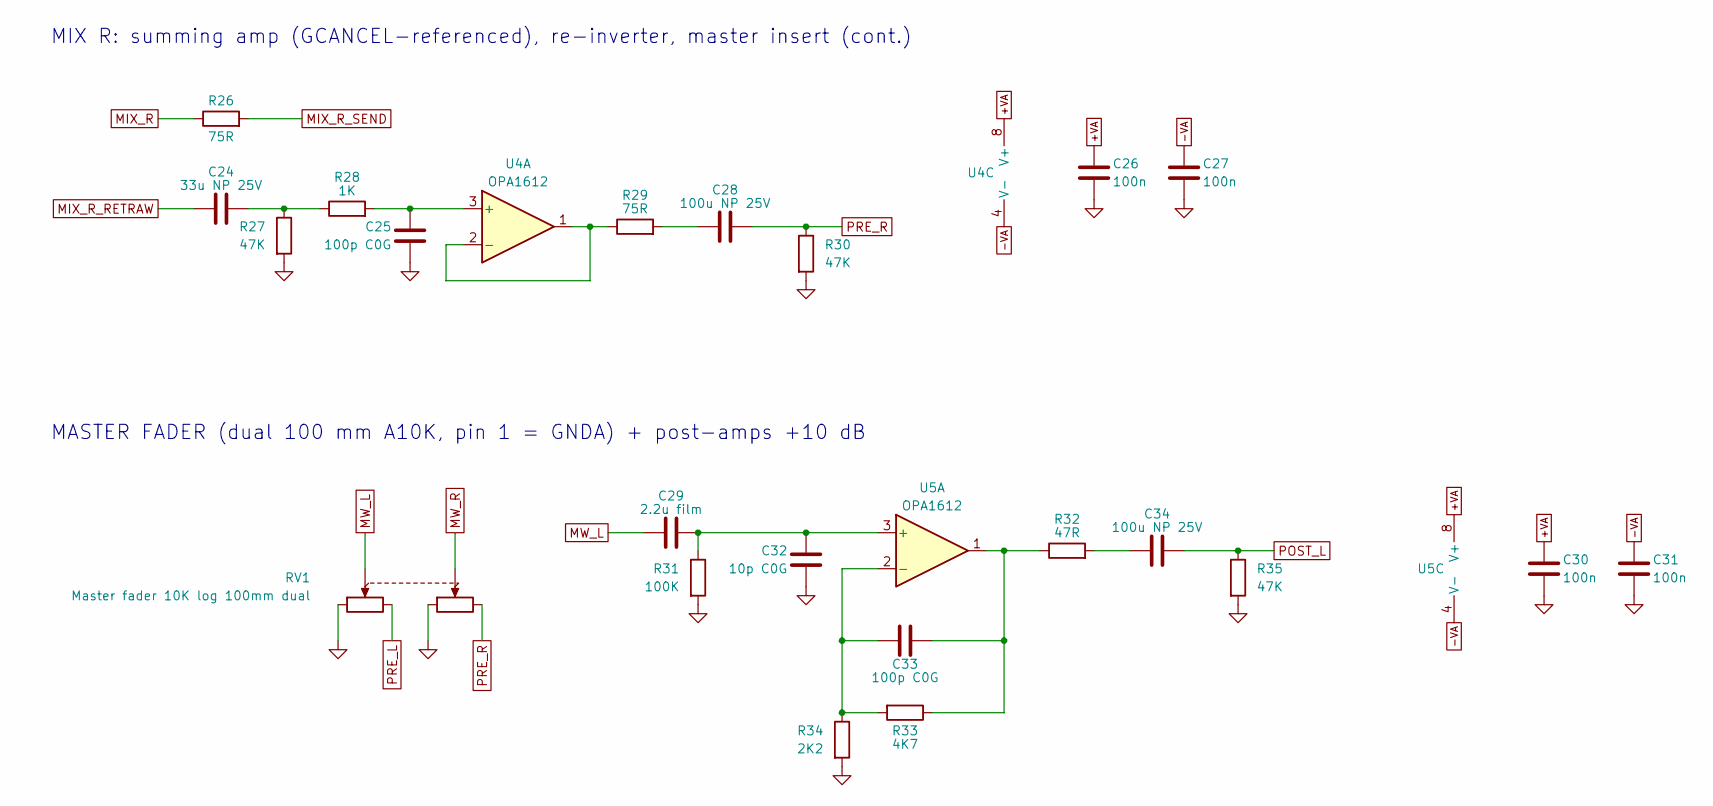
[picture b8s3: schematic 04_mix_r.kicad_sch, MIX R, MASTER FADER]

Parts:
C24: 33u NP 25V; CP_Radial_D8.0mm_P3.50mm; MPN Nichicon UES1E330MPM (MUSE ES)
C25, C33: 100p C0G; C_0805_2012Metric; MPN KEMET C0805C101J5GACTU
C26, C27, C30, C31: 100n; C_0805_2012Metric; MPN Samsung CL21B104KBCNNNC (X7R 50V)
C28, C34: 100u NP 25V; CP_Radial_D10.0mm_P5.00mm; MPN Nichicon UES1E101MPM (MUSE ES)
C29: 2.2u film; C_Rect_L7.2mm_W7.2mm_P5.00mm_FKS2_FKP2_MKS2_MKP2; MPN KEMET MMK5225K63J06L4BULK (PET 63V; rep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
C32: 10p C0G; C_0805_2012Metric; MPN KEMET C0805C100J5GACTU
R26: 75R; R_0805_2012Metric; MPN Panasonic ERJ-P06J750V
R27, R30, R35: 47K; R_0805_2012Metric
R28: 1K; R_0805_2012Metric
R29: 75R; R_0805_2012Metric
R31: 100K; R_0805_2012Metric
R32: 47R; R_0805_2012Metric
R33: 4K7; R_0805_2012Metric
R34: 2K2; R_0805_2012Metric
RV1: Master fader 10K log 100mm dual; Potentiometer_Bourns_PTB0144_Slide_100mm_Dual; MPN Bourns PTB0144-2010BPA103
U4, U5: OPA1612; SOIC-8_3.9x4.9mm_P1.27mm; MPN TI OPA1612AIDR

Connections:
+VA: C26.1, C30.1, U4.8 (V+), U5.8 (V+); also elsewhere on the board
-VA: C27.2, C31.2, U4.4 (V-), U5.4 (V-); also elsewhere on the board
MIX_R: R26.1; also elsewhere on the board
MIX_R_RETRAW: C24.1; also elsewhere on the board
MIX_R_SEND: R26.2; also elsewhere on the board
MW_L: C29.1, RV1.2
MW_R: RV1.5; also elsewhere on the board
unnamed: C24.2, R27.1, R28.1
unnamed: C28.1, R29.2
unnamed: C33.1, R32.1, R33.1, U5.1
unnamed: C34.1, R32.2
unnamed: C25.1, R28.2, U4.3 (+)
unnamed: R29.1, U4.1, U4.2 (-)
unnamed: C29.2, C32.1, R31.1, U5.3 (+)
unnamed: C33.2, R33.2, R34.1, U5.2 (-)
POST_L: C34.2, R35.1; also elsewhere on the board
PRE_L: RV1.3; also elsewhere on the board
PRE_R: C28.2, R30.1, RV1.6

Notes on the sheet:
MIX R: summing amp (GCANCEL-referenced), re-inverter, master insert (cont.)
MASTER FADER (dual 100 mm A10K, pin 1 = GNDA) + post-amps +10 dB

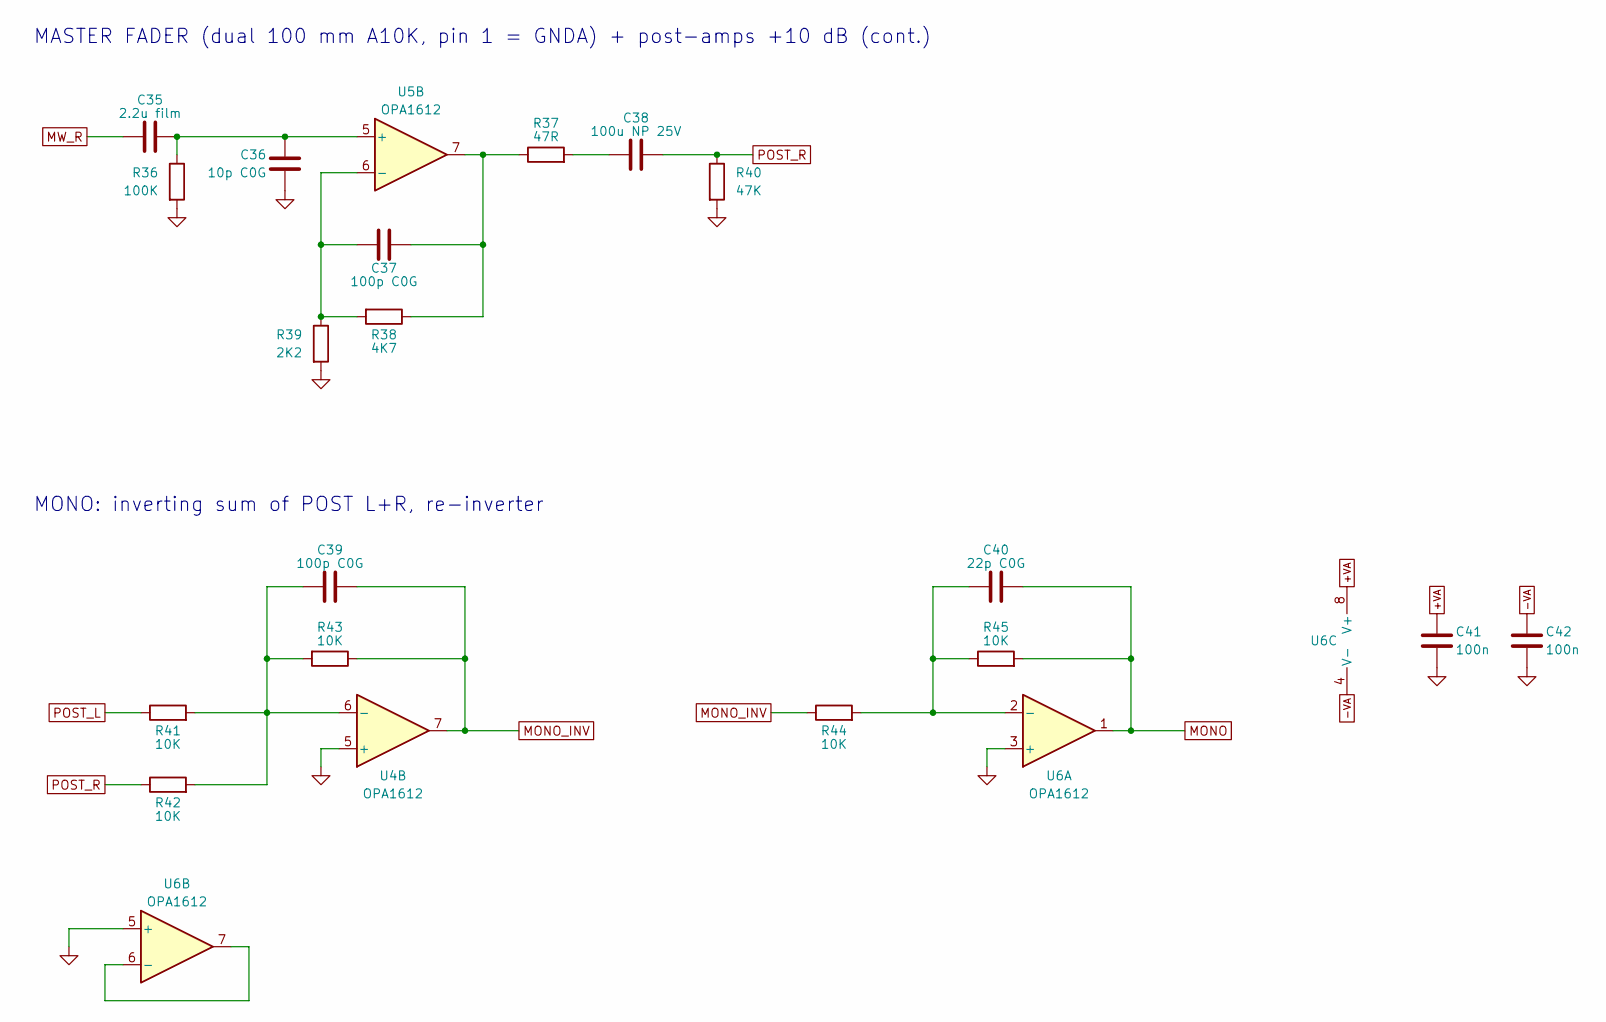
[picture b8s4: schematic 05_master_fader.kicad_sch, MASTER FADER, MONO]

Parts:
C35: 2.2u film; C_Rect_L7.2mm_W7.2mm_P5.00mm_FKS2_FKP2_MKS2_MKP2; MPN KEMET MMK5225K63J06L4BULK (PET 63V; rep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
C36: 10p C0G; C_0805_2012Metric; MPN KEMET C0805C100J5GACTU
C37, C39: 100p C0G; C_0805_2012Metric; MPN KEMET C0805C101J5GACTU
C38: 100u NP 25V; CP_Radial_D10.0mm_P5.00mm; MPN Nichicon UES1E101MPM (MUSE ES)
C40: 22p C0G; C_0805_2012Metric; MPN KEMET C0805C220J5GACTU
C41, C42: 100n; C_0805_2012Metric; MPN Samsung CL21B104KBCNNNC (X7R 50V)
R36: 100K; R_0805_2012Metric
R37: 47R; R_0805_2012Metric
R38: 4K7; R_0805_2012Metric
R39: 2K2; R_0805_2012Metric
R40: 47K; R_0805_2012Metric
R41, R42, R43, R44, R45: 10K; R_0805_2012Metric
U4, U5, U6: OPA1612; SOIC-8_3.9x4.9mm_P1.27mm; MPN TI OPA1612AIDR

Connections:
+VA: C41.1, U6.8 (V+); also elsewhere on the board
-VA: C42.2, U6.4 (V-); also elsewhere on the board
MONO: C40.1, R45.2, U6.1; also elsewhere on the board
MONO_INV: C39.1, R43.1, R44.1, U4.7
MW_R: C35.1; also elsewhere on the board
unnamed: C37.1, R37.1, R38.1, U5.7
unnamed: C38.1, R37.2
unnamed: C39.2, R41.2, R42.2, R43.2, U4.6 (-)
unnamed: C35.2, C36.1, R36.1, U5.5 (+)
unnamed: C37.2, R38.2, R39.1, U5.6 (-)
unnamed: C40.2, R44.2, R45.1, U6.2 (-)
unnamed: U6.6 (-), U6.7
POST_L: R41.1; also elsewhere on the board
POST_R: C38.2, R40.1, R42.1; also elsewhere on the board

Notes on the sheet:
MASTER FADER (dual 100 mm A10K, pin 1 = GNDA) + post-amps +10 dB (cont.)
MONO: inverting sum of POST L+R, re-inverter
